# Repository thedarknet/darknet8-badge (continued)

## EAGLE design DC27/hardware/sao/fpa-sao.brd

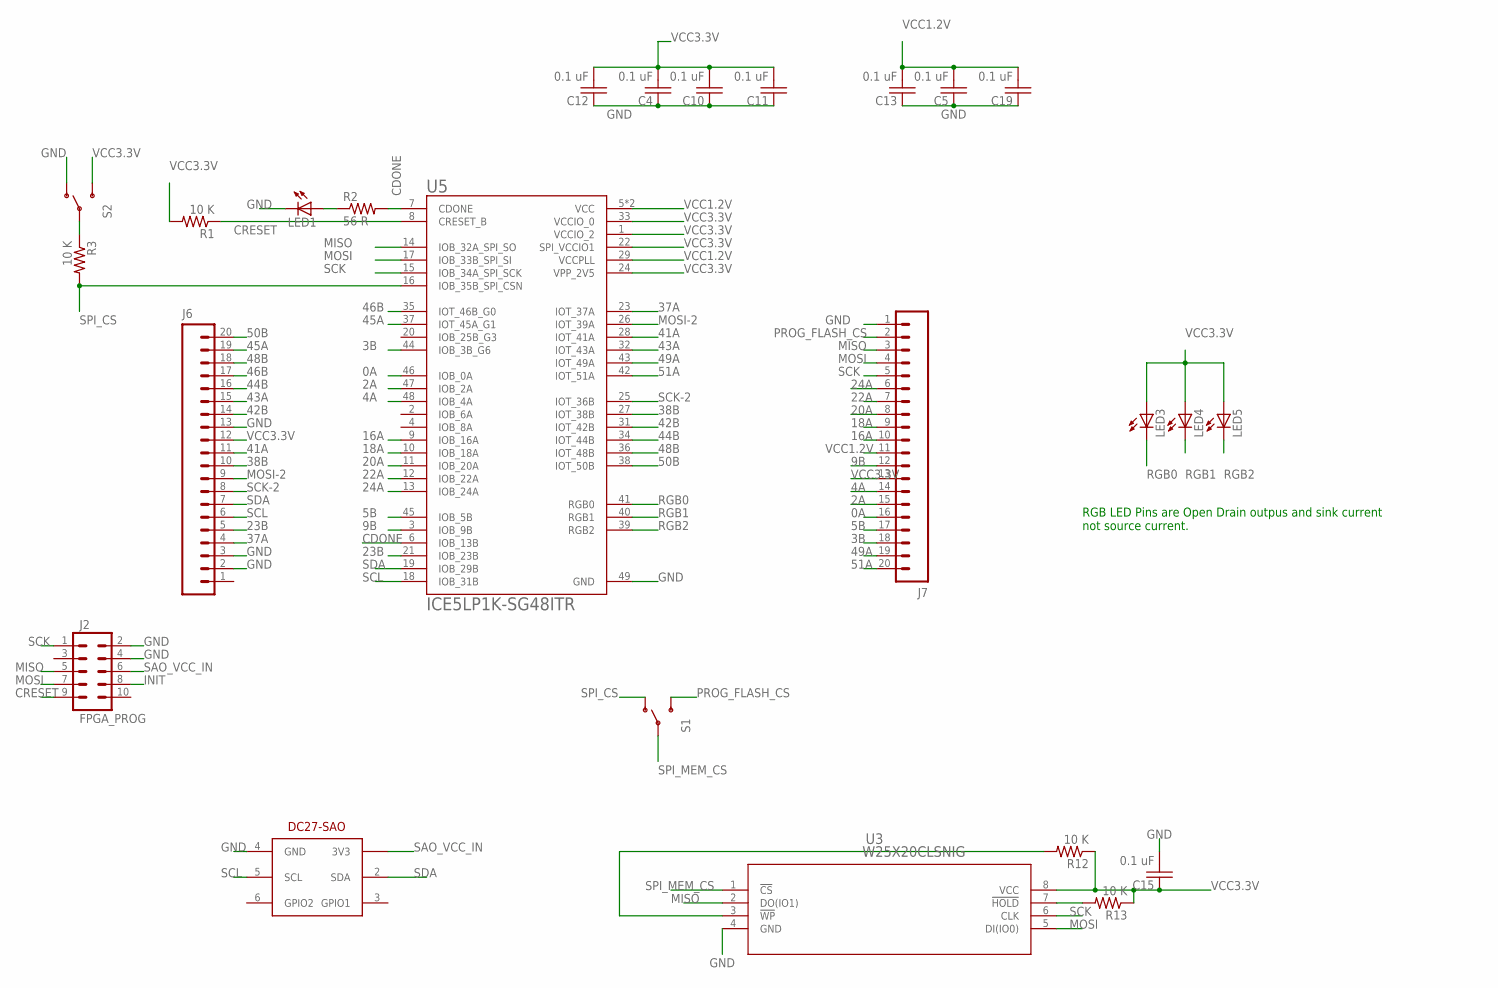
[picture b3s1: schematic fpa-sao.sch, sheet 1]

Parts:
C4, C5, C10, C11, C12, C13, C15, C19: 0.1 uF; C0603
J2: FPGA_PROG; 2X5_NOSILK
J6, J7: M20NO_SILK_KIT; 1X20_NO_SILK_KIT
LED1: LED1206; LED-1206
LED3, LED4, LED5: LED3MM
R1, R3, R12, R13: 10 K; 0805
R2: 56 R; 1206
S1, S2: SWITCH-SPSTKIT; SWITCH-SPDT_KIT
U3: W25X20CLSNIG; WIN_SN-8
U5: ICE5LP1K-SG48ITR; QFN50P700X700X100-49N
U$1: DC-27-SAO; 3X2

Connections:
0A: J7.16, U5.46 (IOB_0A)
2A: J7.15, U5.47 (IOB_2A)
3B: J7.18, U5.44 (IOB_3B_G6)
4A: J7.14, U5.48 (IOB_4A)
5B: J7.17, U5.45 (IOB_5B)
9B: J7.12, U5.3 (IOB_9B)
16A: J7.10, U5.9 (IOB_16A)
18A: J7.9, U5.10 (IOB_18A)
20A: J7.8, U5.11 (IOB_20A)
22A: J7.7, U5.12 (IOB_22A)
23B: J6.5, U5.21 (IOB_23B)
24A: J7.6, U5.13 (IOB_24A)
37A: J6.4, U5.23 (IOT_37A)
38B: J6.10, U5.27 (IOT_38B)
41A: J6.11, U5.28 (IOT_41A)
42B: J6.14, U5.31 (IOT_42B)
43A: J6.15, U5.32 (IOT_43A)
44B: J6.16, U5.34 (IOT_44B)
45A: J6.19, U5.37 (IOT_45A_G1)
46B: J6.17, U5.35 (IOT_46B_G0)
48B: J6.18, U5.36 (IOT_48B)
49A: J7.19, U5.43 (IOT_49A)
50B: J6.20, U5.38 (IOT_50B)
51A: J7.20, U5.42 (IOT_51A)
CDONE: R2.2, U5.6 (IOB_13B), U5.7 (CDONE)
CRESET: J2.9, R1.1, U5.8 (CRESET_B)
GND: C4.1, C5.1, C10.1, C11.1, C12.1, C13.1, C15.2, C19.1, J2.2, J2.4, J6.2, J6.3, J6.13, J7.1, LED1.C, S2.1 (O), U3.4 (GND), U5.49 (GND), U$1.4 (GND); also elsewhere on the board
INIT: J2.8
MISO: J2.5, J7.3, U3.2 (DO(IO1)), U5.14 (IOB_32A_SPI_SO)
MOSI: J2.7, J7.4, U3.5 (DI(IO0)), U5.17 (IOB_33B_SPI_SI); also elsewhere on the board
MOSI-2: J6.9, U5.26 (IOT_39A); also elsewhere on the board
unnamed: LED1.A, R2.1
unnamed: R3.1, S2.2
unnamed: R12.2, U3.3 (!WP)
unnamed: R13.2, U3.7 (!HOLD)
PROG_FLASH_CS: J7.2, S1.3 (S)
RGB0: LED3.K (C), U5.41 (RGB0)
RGB1: LED4.K (C), U5.40 (RGB1)
RGB2: LED5.K (C), U5.39 (RGB2)
SAO_VCC_IN: J2.6, U$1.1 (3V3); also elsewhere on the board
SCK: J2.1, J7.5, U3.6 (CLK), U5.15 (IOB_34A_SPI_SCK); also elsewhere on the board
SCK-2: J6.8, U5.25 (IOT_36B); also elsewhere on the board
SCL: J6.6, U5.18 (IOB_31B), U$1.5 (SCL)
SDA: J6.7, U5.19 (IOB_29B), U$1.2 (SDA)
SPI_CS: R3.2, S1.1 (O), U5.16 (IOB_35B_SPI_CSN)
SPI_MEM_CS: S1.2, U3.1 (!CS)
VCC1.2V: C5.2, C13.2, C19.2, J7.11, U5.5 (VCC), U5.29 (VCCPLL), U5.30 (VCC); also elsewhere on the board
VCC3.3V: C4.2, C10.2, C11.2, C12.2, C15.1, J6.12, J7.13, LED3.A, LED4.A, LED5.A, R1.2, R12.1, R13.1, S2.3 (S), U3.8 (VCC), U5.1 (VCCIO_2), U5.22 (SPI_VCCIO1), U5.24 (VPP_2V5), U5.33 (VCCIO_0); also elsewhere on the board

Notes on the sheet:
RGB LED Pins are Open Drain outpus and sink current not source current.

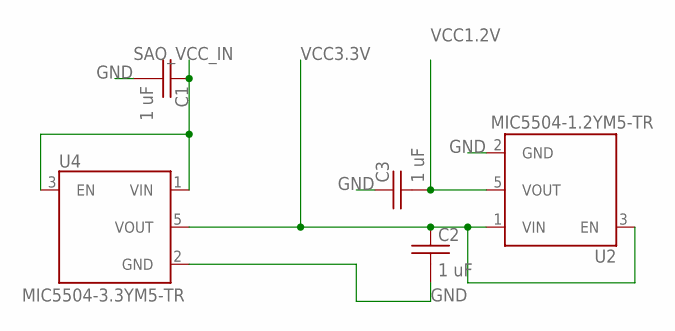
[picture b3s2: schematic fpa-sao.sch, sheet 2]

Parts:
C1, C2, C3: 1 uF; C0603
U2: MIC5504-1.2YM5-TR; SOT23-5P95_280X145XL45X37N
U4: MIC5504-3.3YM5-TR; SOT23-5P95_280X145XL45X37N

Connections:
GND: C1.2, C2.2, C3.1, U2.2 (GND), U4.2 (GND); also elsewhere on the board
SAO_VCC_IN: C1.1, U4.1 (VIN), U4.3 (EN); also elsewhere on the board
VCC1.2V: C3.2, U2.5 (VOUT); also elsewhere on the board
VCC3.3V: C2.1, U2.1 (VIN), U2.3 (EN), U4.5 (VOUT); also elsewhere on the board

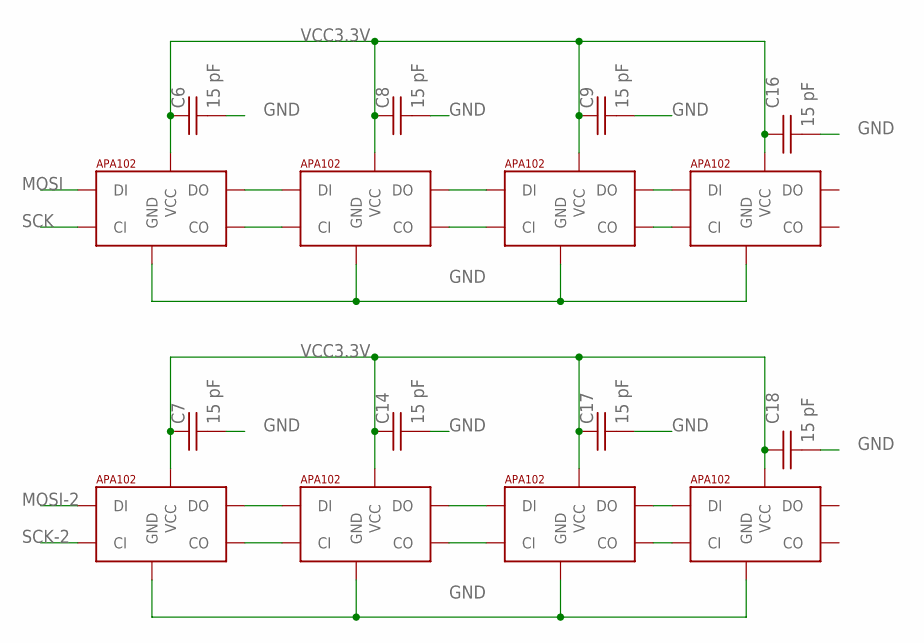
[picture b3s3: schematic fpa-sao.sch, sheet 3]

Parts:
C6, C7, C8, C9, C14, C16, C17, C18: 15 pF; C1206
U$2, U$3, U$4, U$5, U$6, U$7, U$8, U$10: APA1025050; APA102_5050

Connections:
GND: C6.2, C7.2, C8.2, C9.2, C14.2, C16.2, C17.2, C18.2, U$2.6 (GND), U$3.6 (GND), U$4.6 (GND), U$5.6 (GND), U$6.6 (GND), U$7.6 (GND), U$8.6 (GND), U$10.6 (GND); also elsewhere on the board
MOSI: U$6.4 (DI); also elsewhere on the board
MOSI-2: U$2.4 (DI); also elsewhere on the board
unnamed: U$6.2 (CO), U$7.5 (CI)
unnamed: U$6.3 (DO), U$7.4 (DI)
unnamed: U$7.3 (DO), U$8.4 (DI)
unnamed: U$7.2 (CO), U$8.5 (CI)
unnamed: U$2.2 (CO), U$3.5 (CI)
unnamed: U$8.3 (DO), U$10.4 (DI)
unnamed: U$8.2 (CO), U$10.5 (CI)
unnamed: U$2.3 (DO), U$3.4 (DI)
unnamed: U$3.3 (DO), U$4.4 (DI)
unnamed: U$3.2 (CO), U$4.5 (CI)
unnamed: U$4.3 (DO), U$5.4 (DI)
unnamed: U$4.2 (CO), U$5.5 (CI)
SCK: U$6.5 (CI); also elsewhere on the board
SCK-2: U$2.5 (CI); also elsewhere on the board
VCC3.3V: C6.1, C7.1, C8.1, C9.1, C14.1, C16.1, C17.1, C18.1, U$2.1 (VCC), U$3.1 (VCC), U$4.1 (VCC), U$5.1 (VCC), U$6.1 (VCC), U$7.1 (VCC), U$8.1 (VCC), U$10.1 (VCC); also elsewhere on the board

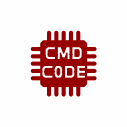
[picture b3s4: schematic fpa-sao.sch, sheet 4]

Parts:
U$9: CMD_C0DE_LOGOCMD_CODE_LOGO_SILK; CMD_C0DE_LOGO_SILK

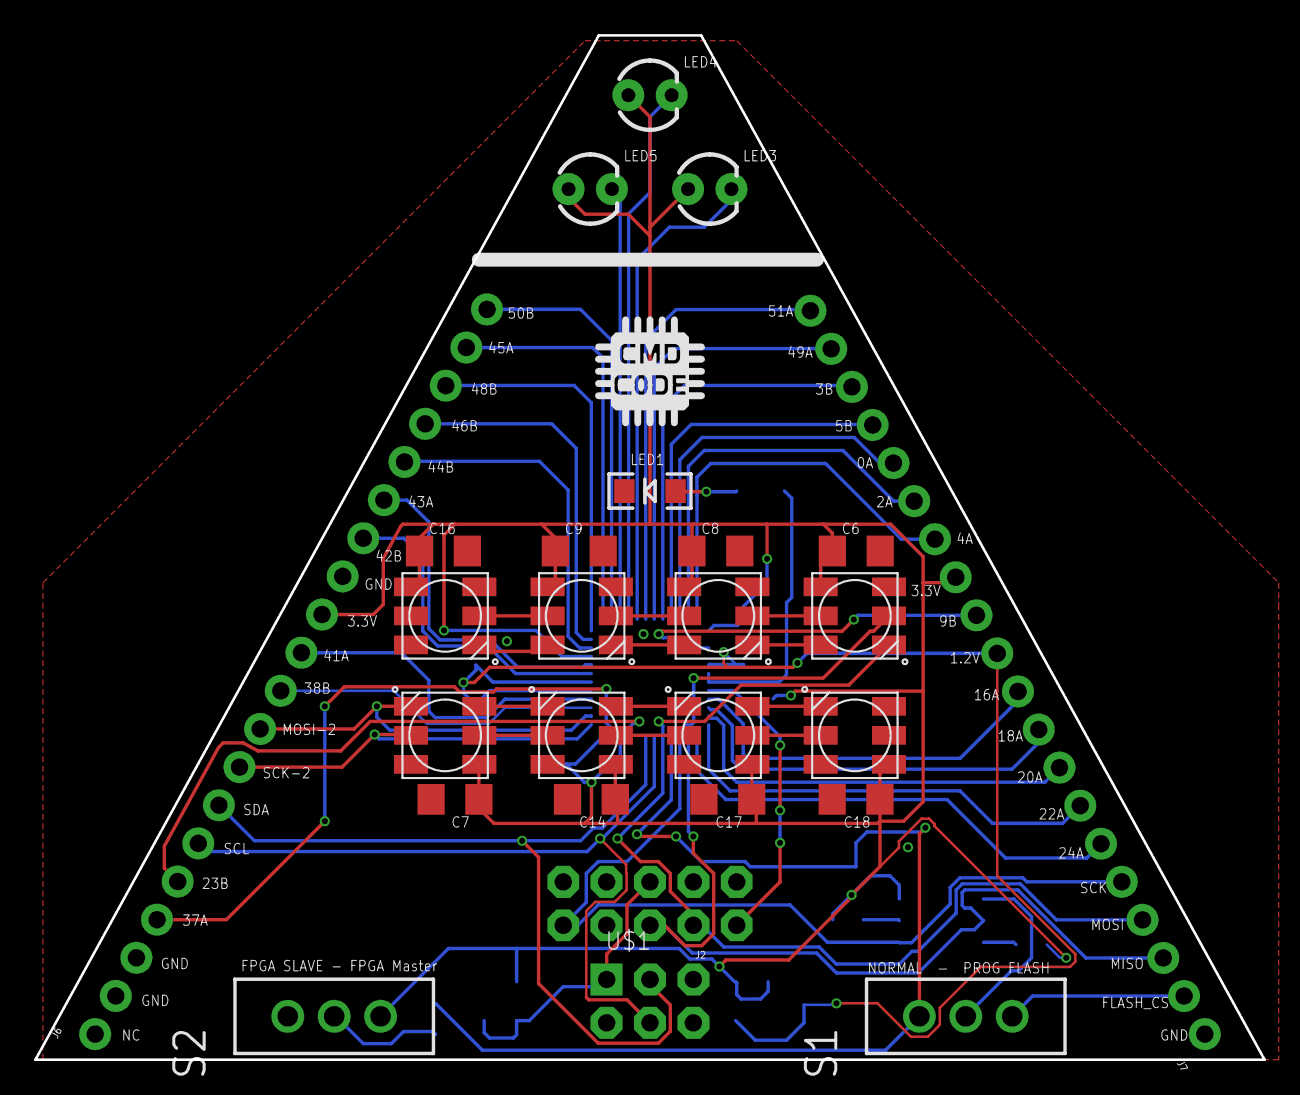
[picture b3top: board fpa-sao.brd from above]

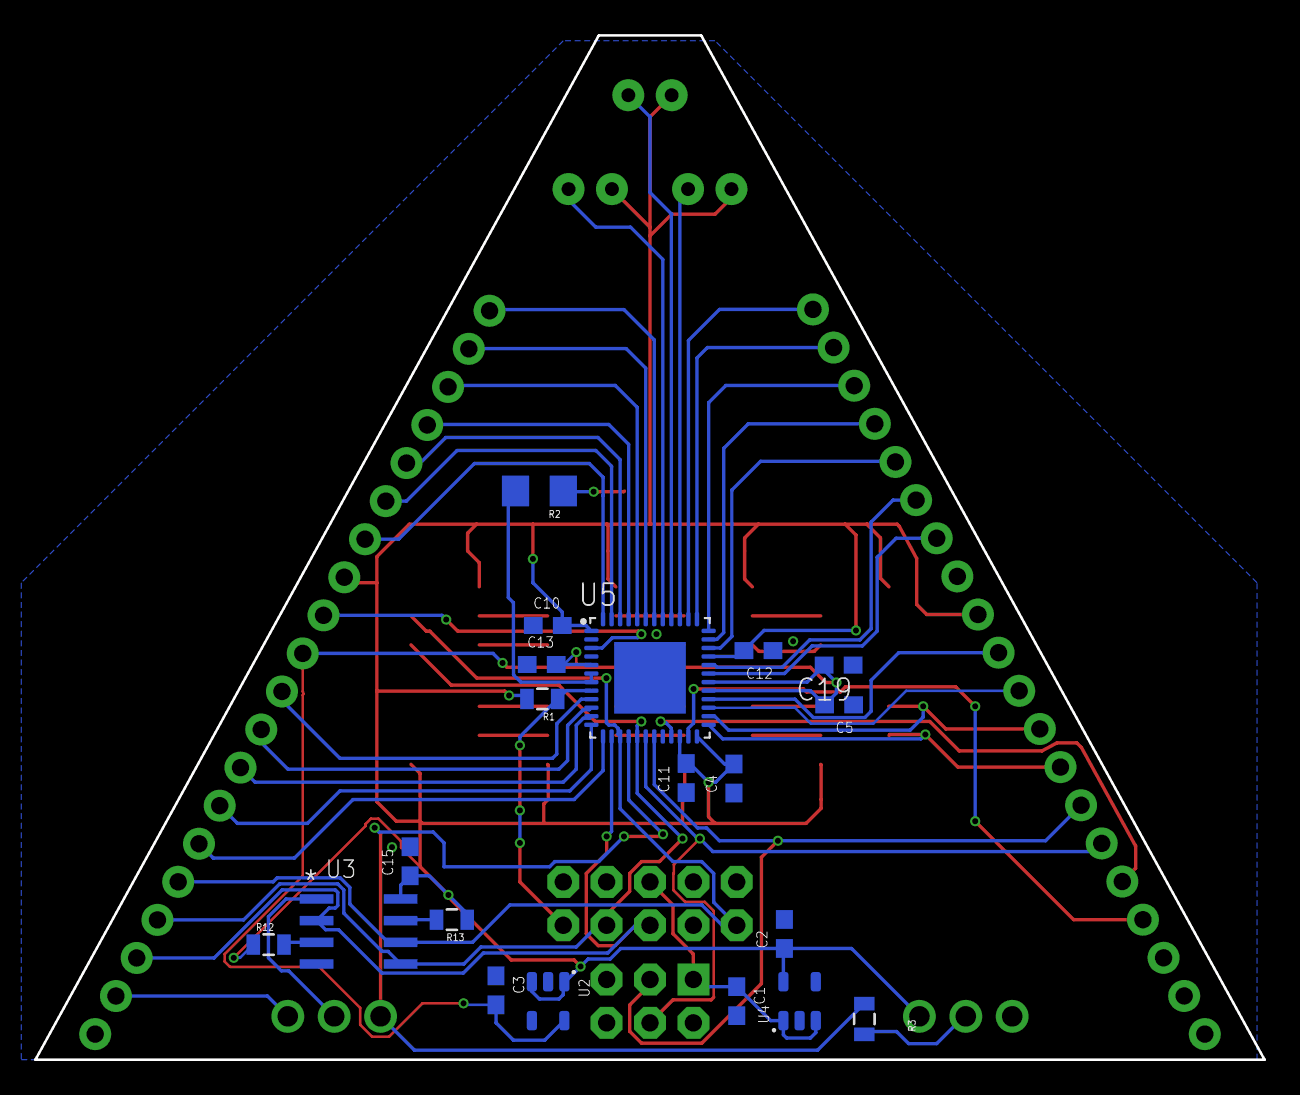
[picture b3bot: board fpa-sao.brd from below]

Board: 2 copper layers, 72.0 x 60.0 mm, 47 parts (20 on the bottom side), 59 nets.

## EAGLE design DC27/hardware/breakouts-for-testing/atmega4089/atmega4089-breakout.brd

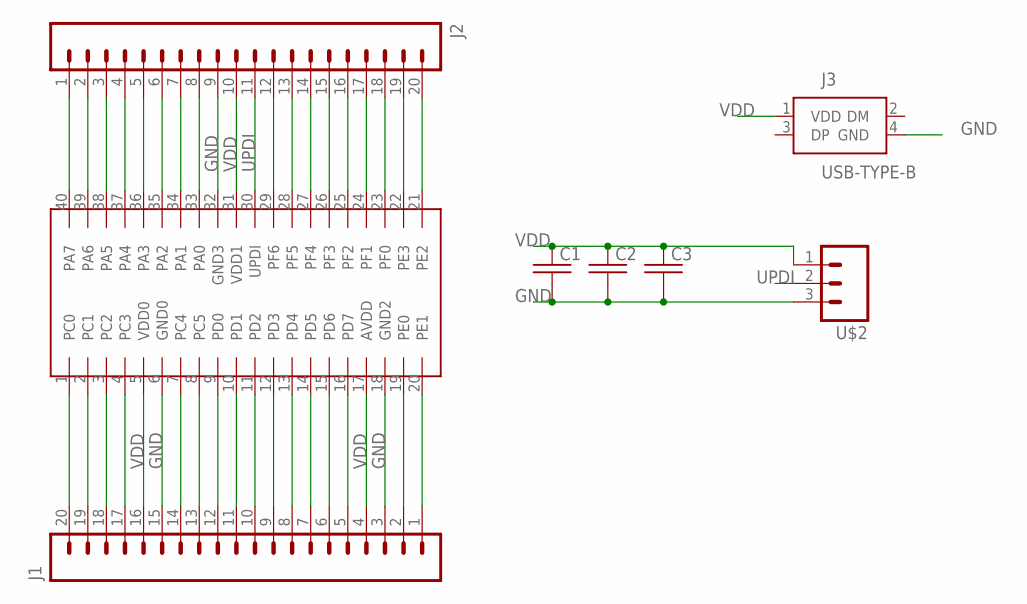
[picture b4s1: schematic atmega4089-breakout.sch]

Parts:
C1, C2, C3: C-USC0805; C0805
J1, J2: M20; 1X20
J3: USB-TYPE-B; 61400413321
U$1: ATMEGA4809-PFATMEL4809-PF; DIP1587W58P254L5175H635Q40B
U$2: M03; 1X03_UDPI

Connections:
GND: C1.2, C2.2, C3.2, J1.3, J1.15, J2.9, J3.4 (GND), U$1.6 (GND0), U$1.18 (GND2), U$1.32 (GND3), U$2.3
unnamed: J2.1, U$1.40 (PA7)
unnamed: J2.2, U$1.39 (PA6)
unnamed: J2.3, U$1.38 (PA5)
unnamed: J2.4, U$1.37 (PA4)
unnamed: J2.5, U$1.36 (PA3)
unnamed: J2.6, U$1.35 (PA2)
unnamed: J2.7, U$1.34 (PA1)
unnamed: J2.8, U$1.33 (PA0)
unnamed: J2.12, U$1.29 (PF6)
unnamed: J2.13, U$1.28 (PF5)
unnamed: J2.14, U$1.27 (PF4)
unnamed: J2.15, U$1.26 (PF3)
unnamed: J2.16, U$1.25 (PF2)
unnamed: J2.17, U$1.24 (PF1)
unnamed: J2.18, U$1.23 (PF0)
unnamed: J2.19, U$1.22 (PE3)
unnamed: J2.20, U$1.21 (PE2)
unnamed: J1.1, U$1.20 (PE1)
unnamed: J1.2, U$1.19 (PE0)
unnamed: J1.5, U$1.16 (PD7)
unnamed: J1.6, U$1.15 (PD6)
unnamed: J1.7, U$1.14 (PD5)
unnamed: J1.8, U$1.13 (PD4)
unnamed: J1.9, U$1.12 (PD3)
unnamed: J1.10, U$1.11 (PD2)
unnamed: J1.11, U$1.10 (PD1)
unnamed: J1.12, U$1.9 (PD0)
unnamed: J1.13, U$1.8 (PC5)
unnamed: J1.14, U$1.7 (PC4)
unnamed: J1.17, U$1.4 (PC3)
unnamed: J1.18, U$1.3 (PC2)
unnamed: J1.19, U$1.2 (PC1)
unnamed: J1.20, U$1.1 (PC0)
UPDI: J2.11, U$1.30 (UPDI), U$2.2
VDD: C1.1, C2.1, C3.1, J1.4, J1.16, J2.10, J3.1 (VDD), U$1.5 (VDD0), U$1.17 (AVDD), U$1.31 (VDD1), U$2.1

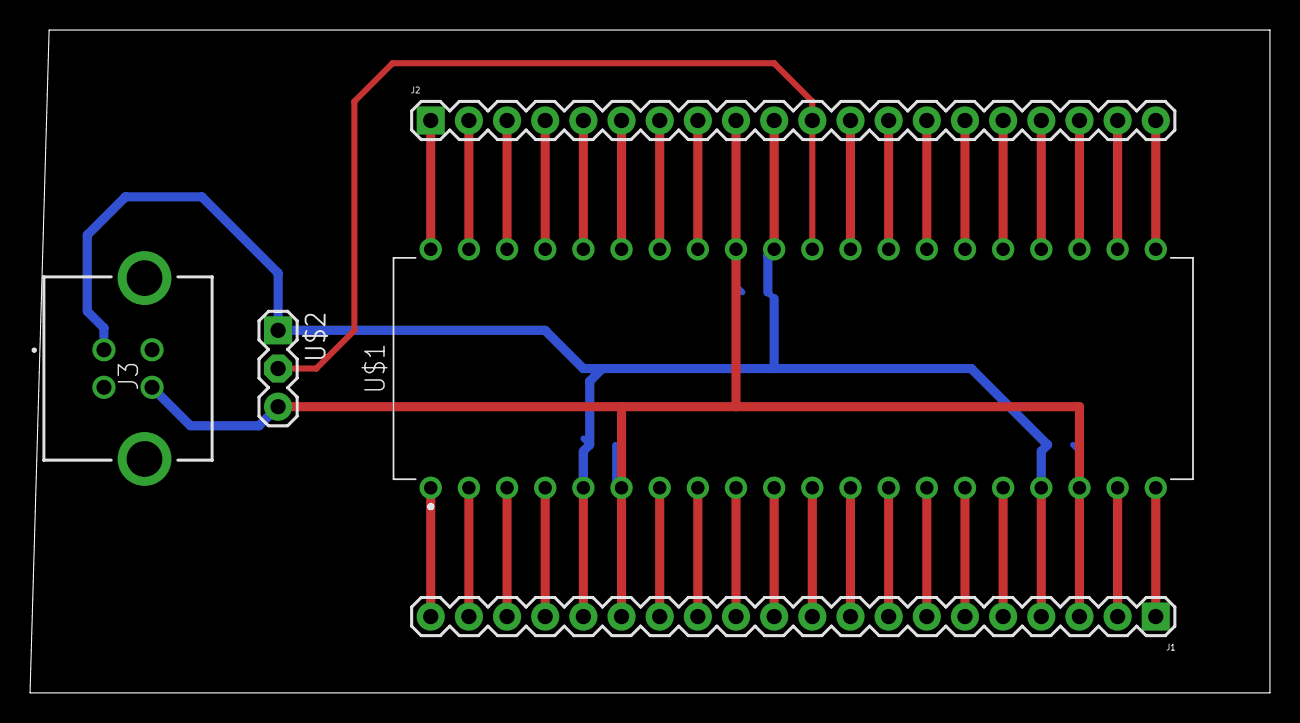
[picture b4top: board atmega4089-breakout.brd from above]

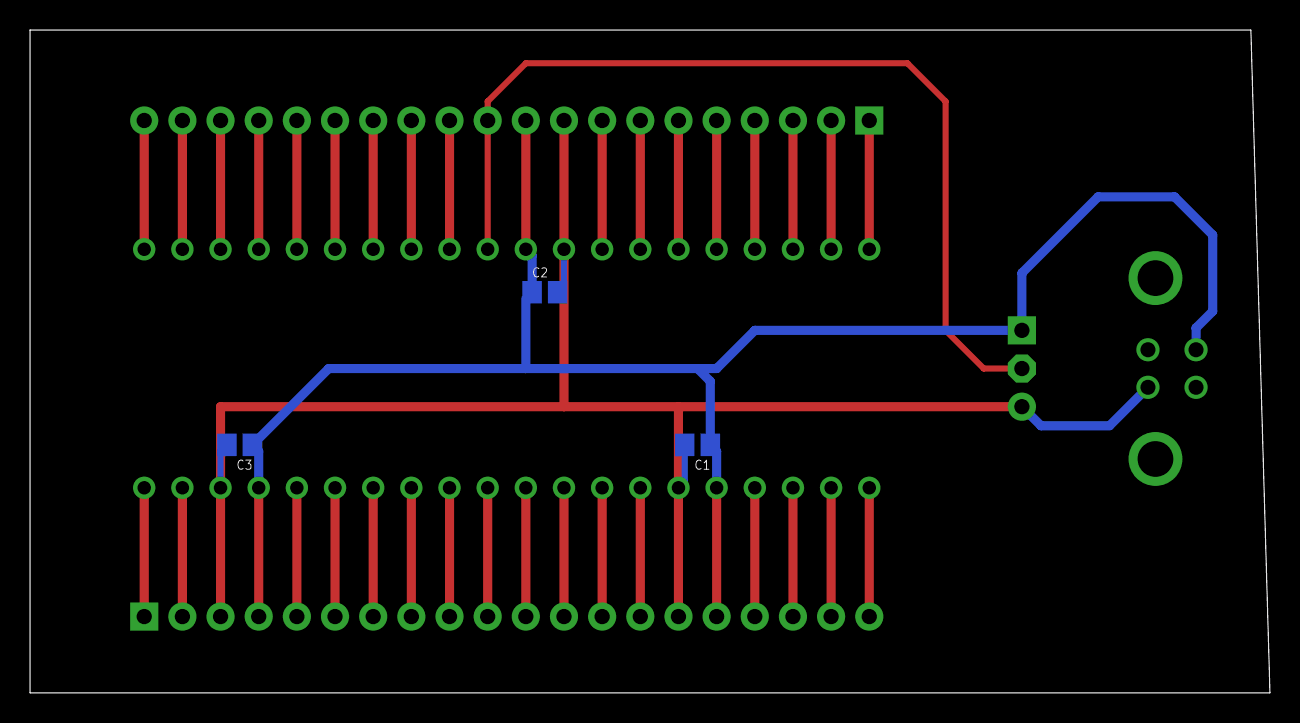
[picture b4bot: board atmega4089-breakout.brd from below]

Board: 2 copper layers, 82.5 x 44.1 mm, 8 parts (3 on the bottom side), 36 nets.

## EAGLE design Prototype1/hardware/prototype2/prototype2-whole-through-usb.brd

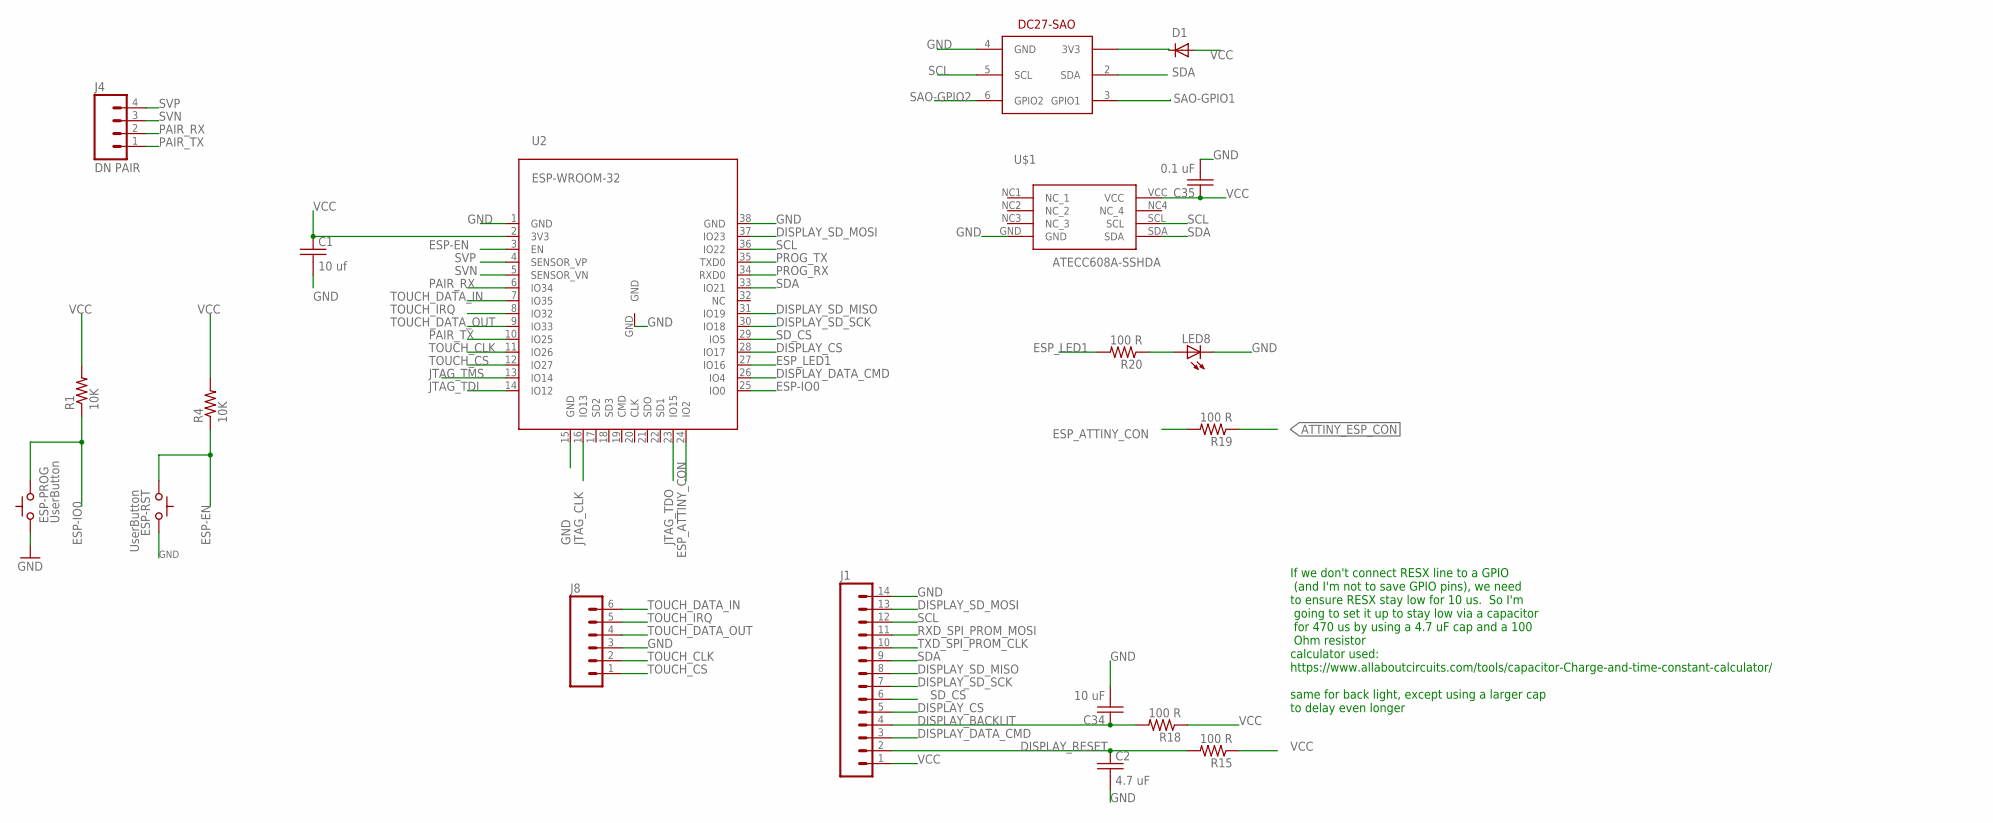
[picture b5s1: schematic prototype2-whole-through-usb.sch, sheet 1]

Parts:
C1: 10 uf; C0805
C2: 4.7 uF; C0805
C34: 10 uF; C0805
C35: 0.1 uF; C0805
D1: DIODESMA; SMA-DIODE
ESP-PROG: UserButton; TACTILE-2PIN-NARROW
ESP-RST: UserButton; TACTILE-2PIN-NARROW
J1: M14; 1X14
J4: DN PAIR; 1X04
J8: M06NO_SILK_YES_STOP; 1X06_NO_SILK_YES_STOP
LED8: LED3MM
R1, R4: 10K; 0805
R15, R18, R19, R20: 100 R; 0805
U2: ESP-WROOM-32
U$1: ATECC608A-SSHDA; 8-SOIC
U$4: DC-27-SAO; 3X2

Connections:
ATTINY_ESP_CON: R19.1; also elsewhere on the board
DISPLAY_BACKLIT: C34.1, J1.4, R18.2
DISPLAY_CS: J1.5, U2.28 (IO17)
DISPLAY_DATA_CMD: J1.3, U2.26 (IO4)
DISPLAY_RESET: C2.1, J1.2, R15.2
DISPLAY_SD_MISO: J1.8, U2.31 (IO19)
DISPLAY_SD_MOSI: J1.13, U2.37 (IO23)
DISPLAY_SD_SCK: J1.7, U2.30 (IO18)
ESP-EN: ESP-RST.P$2 (C), R4.1, U2.3 (EN)
ESP-IO0: ESP-PROG.P$1 (A), R1.1, U2.25 (IO0)
ESP_ATTINY_CON: R19.2, U2.24 (IO2)
ESP_LED1: R20.2, U2.27 (IO16)
GND: C1.2, C2.2, C34.2, C35.2, ESP-PROG.P$2 (C), ESP-RST.P$1 (A), J1.14, J8.3, LED8.K (C), U2.1 (GND), U2.15 (GND), U2.38 (GND), U2.GND, U$1.GND, U$4.4 (GND); also elsewhere on the board
JTAG_CLK: U2.16 (IO13); also elsewhere on the board
JTAG_TDI: U2.14 (IO12); also elsewhere on the board
JTAG_TDO: U2.23 (IO15); also elsewhere on the board
JTAG_TMS: U2.13 (IO14); also elsewhere on the board
unnamed: D1.C, U$4.1 (3V3)
unnamed: LED8.A, R20.1
PAIR_RX: J4.2, U2.6 (IO34)
PAIR_TX: J4.1, U2.10 (IO25)
PROG_RX: U2.34 (RXD0); also elsewhere on the board
PROG_TX: U2.35 (TXD0); also elsewhere on the board
RXD_SPI_PROM_MOSI: J1.11; also elsewhere on the board
SAO-GPIO1: U$4.3 (GPIO1)
SAO-GPIO2: U$4.6 (GPIO2)
SCL: J1.12, U2.36 (IO22), U$1.SCL, U$4.5 (SCL)
SDA: J1.9, U2.33 (IO21), U$1.SDA, U$4.2 (SDA)
SD_CS: J1.6, U2.29 (IO5)
SVN: J4.3, U2.5 (SENSOR_VN)
SVP: J4.4, U2.4 (SENSOR_VP)
TOUCH_CLK: J8.2, U2.11 (IO26)
TOUCH_CS: J8.1, U2.12 (IO27)
TOUCH_DATA_IN: J8.6, U2.7 (IO35)
TOUCH_DATA_OUT: J8.4, U2.9 (IO33)
TOUCH_IRQ: J8.5, U2.8 (IO32)
TXD_SPI_PROM_CLK: J1.10; also elsewhere on the board
VCC: C1.1, C35.1, D1.A, J1.1, R1.2, R4.2, R15.1, R18.1, U2.2 (3V3), U$1.VCC; also elsewhere on the board

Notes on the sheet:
If we don't connect RESX line to a GPIO (and I'm not to save GPIO pins), we need to ensure RESX stay low for 10 us. So I'm going to set it up to stay low via a capacitor for 470 us by using a 4.7 uF cap and a 100 Ohm resistor calculator used: https://www.allaboutcircuits.com/tools/capacitor-Charge-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

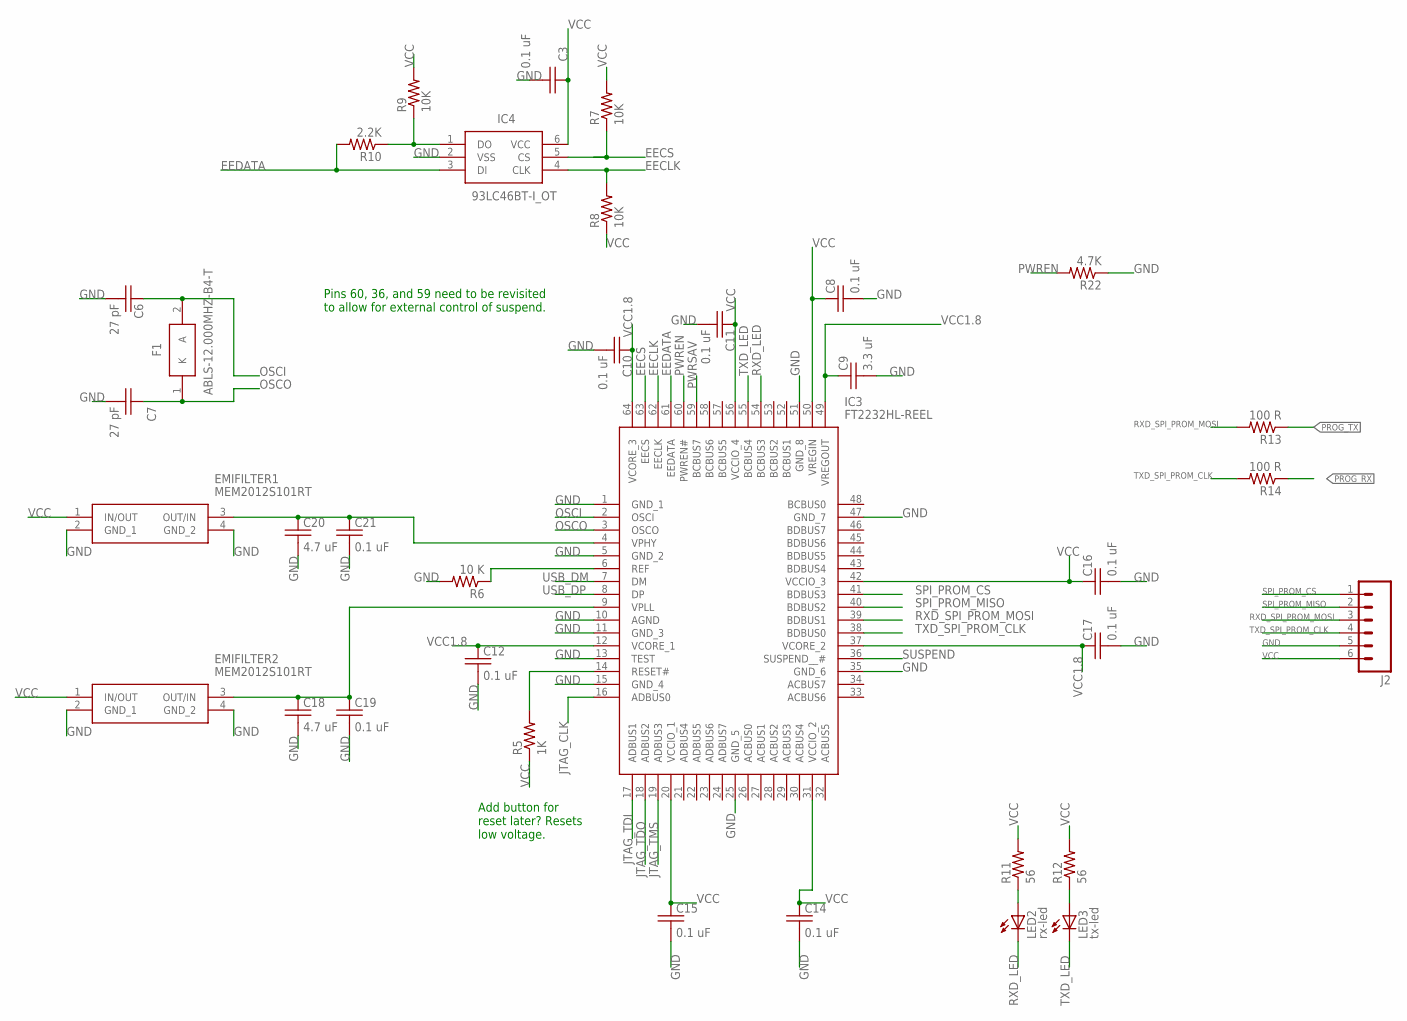
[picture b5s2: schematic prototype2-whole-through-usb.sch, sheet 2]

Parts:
C3, C8, C10, C11, C12, C14, C15, C16, C17, C19, C21: 0.1 uF; C0805
C6, C7: 27 pF; C0805
C9: 3.3 uF; C0805
C18, C20: 4.7 uF; C0805
EMIFILTER1, EMIFILTER2: MEM2012S101RT
F1: ABLS-12.000MHZ-B4-T; HC/49US-(AT49)_1
IC3: FT2232HL-REEL; QFP50P1200X1200X160-64N
IC4: 93LC46BT-I_OT; SOT95P270X145-6N
J2: M06SILK_FEMALE_PTH; 1X06
LED2: rx-led; LED3MM
LED3: tx-led; LED3MM
R5: 1K; 0805
R6: 10 K; 0805
R7, R8, R9: 10K; 0805
R10: 2.2K; 0805
R11, R12: 56; 0805
R13, R14: 100 R; 0805
R22: 4.7K; 0805

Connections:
EECLK: IC3.62 (EECLK), IC4.4 (CLK), R8.2
EECS: IC3.63 (EECS), IC4.5 (CS), R7.1
EEDATA: IC3.61 (EEDATA), IC4.3 (DI), R10.2
GND: C3.2, C6.2, C7.2, C8.2, C9.2, C10.2, C11.2, C12.2, C14.2, C15.2, C16.2, C17.2, C18.2, C19.2, C20.2, C21.2, EMIFILTER1.2 (GND_1), EMIFILTER1.4 (GND_2), EMIFILTER2.2 (GND_1), EMIFILTER2.4 (GND_2), IC3.1 (GND_1), IC3.5 (GND_2), IC3.10 (AGND), IC3.11 (GND_3), IC3.13 (TEST), IC3.15 (GND_4), IC3.25 (GND_5), IC3.35 (GND_6), IC3.47 (GND_7), IC3.51 (GND_8), IC4.2 (VSS), J2.5, R6.2, R22.1; also elsewhere on the board
JTAG_CLK: IC3.16 (ADBUS0); also elsewhere on the board
JTAG_TDI: IC3.17 (ADBUS1); also elsewhere on the board
JTAG_TDO: IC3.18 (ADBUS2); also elsewhere on the board
JTAG_TMS: IC3.19 (ADBUS3); also elsewhere on the board
unnamed: IC3.14 (RESET#), R5.2
unnamed: IC3.6 (REF), R6.1
unnamed: IC4.1 (DO), R9.1, R10.1
unnamed: LED2.A, R11.1
unnamed: LED3.A, R12.1
unnamed: C18.1, C19.1, EMIFILTER2.3 (OUT/IN), IC3.9 (VPLL)
unnamed: C20.1, C21.1, EMIFILTER1.3 (OUT/IN), IC3.4 (VPHY)
OSCI: C6.1, F1.2 (A), IC3.2 (OSCI)
OSCO: C7.1, F1.1 (K), IC3.3 (OSCO)
PROG_RX: R14.1; also elsewhere on the board
PROG_TX: R13.1; also elsewhere on the board
PWREN: IC3.60 (PWREN#), R22.2
PWRSAV: IC3.59 (BCBUS7)
RXD_LED: IC3.54 (BCBUS3), LED2.K (C)
RXD_SPI_PROM_MOSI: IC3.39 (BDBUS1), J2.3, R13.2; also elsewhere on the board
SPI_PROM_CS: IC3.41 (BDBUS3), J2.1
SPI_PROM_MISO: IC3.40 (BDBUS2), J2.2
SUSPEND: IC3.36 (SUSPEND__#)
TXD_LED: IC3.55 (BCBUS4), LED3.K (C)
TXD_SPI_PROM_CLK: IC3.38 (BDBUS0), J2.4, R14.2; also elsewhere on the board
USB_DM: IC3.7 (DM); also elsewhere on the board
USB_DP: IC3.8 (DP); also elsewhere on the board
VCC: C3.1, C8.1, C11.1, C14.1, C15.1, C16.1, EMIFILTER1.1 (IN/OUT), EMIFILTER2.1 (IN/OUT), IC3.20 (VCCIO_1), IC3.31 (VCCIO_2), IC3.42 (VCCIO_3), IC3.50 (VREGIN), IC3.56 (VCCIO_4), IC4.6 (VCC), J2.6, R5.1, R7.2, R8.1, R9.2, R11.2, R12.2; also elsewhere on the board
VCC1.8: C9.1, C10.1, C12.1, C17.1, IC3.12 (VCORE_1), IC3.37 (VCORE_2), IC3.49 (VREGOUT), IC3.64 (VCORE_3)

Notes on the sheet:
Add button for reset later? Resets low voltage.
Pins 60, 36, and 59 need to be revisited to allow for external control of suspend.

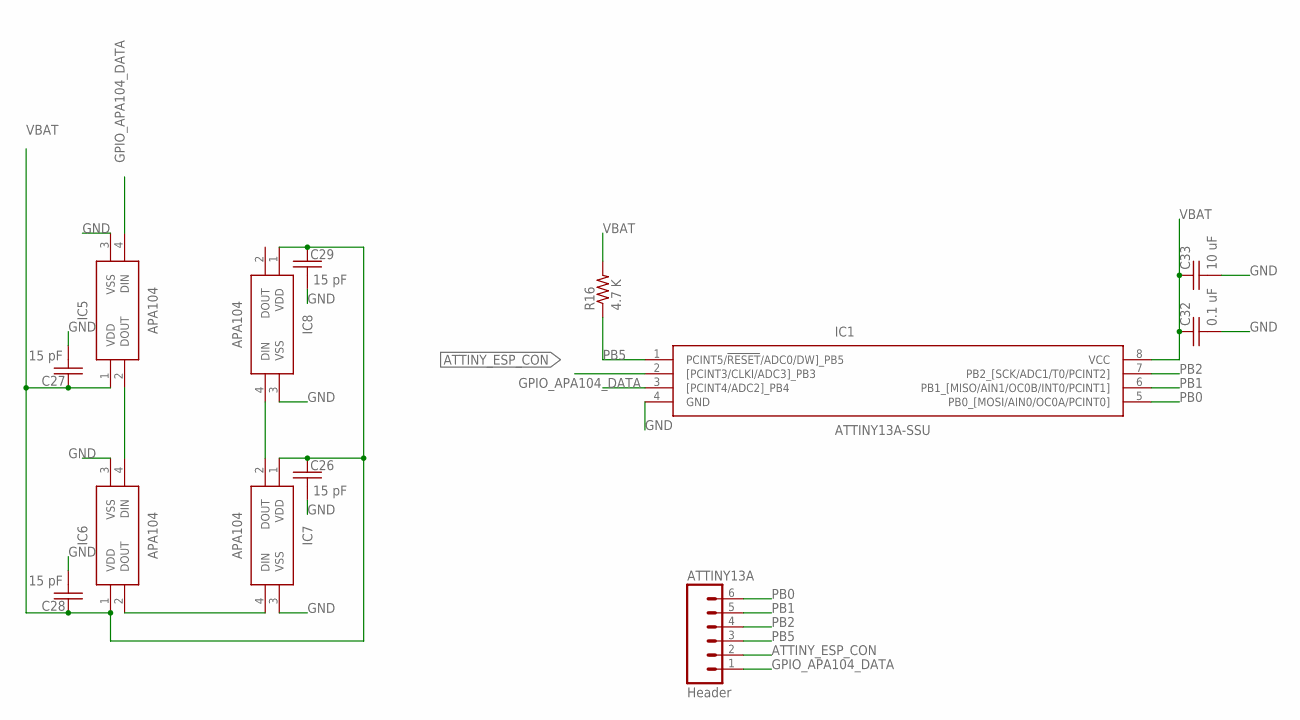
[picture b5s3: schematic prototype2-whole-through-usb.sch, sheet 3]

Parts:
ATTINY13A: Header; 1X06
C26, C27, C28, C29: 15 pF; C0805
C32: 0.1 uF; C0805
C33: 10 uF; C0805
IC1: ATTINY13A-SSU; SOIC127P600X175-8N
IC5, IC6, IC7, IC8: APA104
R16: 4.7 K; 0805

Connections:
ATTINY_ESP_CON: ATTINY13A.2, IC1.2 ([PCINT3/CLKI/ADC3]_PB3); also elsewhere on the board
GND: C26.2, C27.2, C28.2, C29.2, C32.2, C33.2, IC1.4 (GND), IC5.3 (VSS), IC6.3 (VSS), IC7.3 (VSS), IC8.3 (VSS); also elsewhere on the board
GPIO_APA104_DATA: ATTINY13A.1, IC1.3 ([PCINT4/ADC2]_PB4), IC5.4 (DIN)
unnamed: IC5.2 (DOUT), IC6.4 (DIN)
unnamed: IC6.2 (DOUT), IC7.4 (DIN)
unnamed: IC7.2 (DOUT), IC8.4 (DIN)
PB0: ATTINY13A.6, IC1.5 (PB0_[MOSI/AIN0/OC0A/PCINT0])
PB1: ATTINY13A.5, IC1.6 (PB1_[MISO/AIN1/OC0B/INT0/PCINT1])
PB2: ATTINY13A.4, IC1.7 (PB2_[SCK/ADC1/T0/PCINT2])
PB5: ATTINY13A.3, IC1.1 (PCINT5/!RESET!/ADC0/DW]_PB5), R16.1
VBAT: C26.1, C27.1, C28.1, C29.1, C32.1, C33.1, IC1.8 (VCC), IC5.1 (VDD), IC6.1 (VDD), IC7.1 (VDD), IC8.1 (VDD), R16.2; also elsewhere on the board

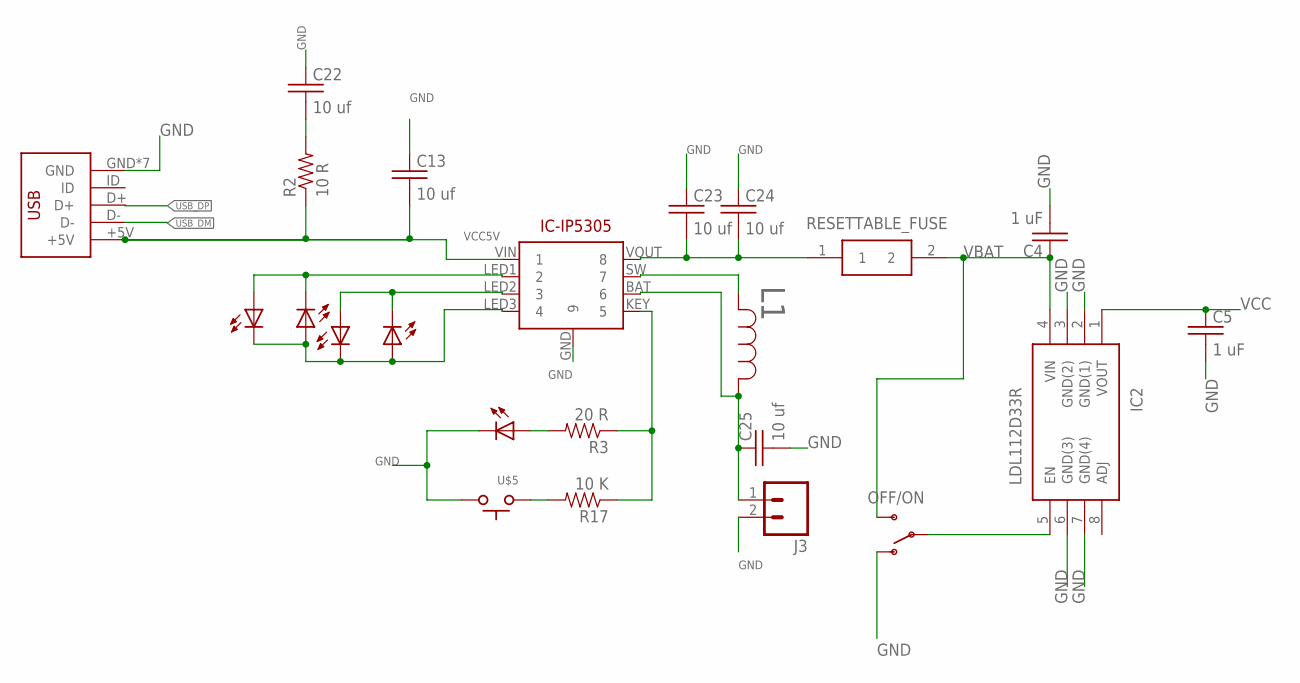
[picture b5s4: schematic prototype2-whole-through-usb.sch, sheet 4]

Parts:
C4, C5: 1 uF; C0805
C13, C22, C23, C24, C25: 10 uf; C0805
IC2: LDL112D33R; SOIC127P600X175-8N
IC-IP5305: IP5305ESOP8; SOIC127P600X165-8
J3: M02PTH; 1X02
L1: NRS4018T2R2MDGJ; IND_TAIYO_NRS4018
LED1, LED4, LED5, LED6, LED7: LED3MM
OFF/ON: SWITCH-SPSTKIT; SWITCH-SPDT_KIT
R2: 10 R; 0805
R3: 20 R; 0805
R17: 10 K; 0805
RESETTABLE_FUSE: 0ZCJ0050FF2G; FUSC3216X55N
U$2: DX4R005JJ2DX4R005JJ2; DX4R005JJ2
U$5: SWITCH_TACTILETACTILE-2PIN-NARROW; TACTILE-2PIN-NARROW

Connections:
GND: C4.2, C5.2, C13.1, C22.1, C23.1, C24.1, C25.2, IC2.2 (GND(1)), IC2.3 (GND(2)), IC2.6 (GND(3)), IC2.7 (GND(4)), IC-IP5305.GND (9), J3.2, LED7.K (C), OFF/ON.1 (O), U$2.GND, U$2.P$6 (GND), U$2.P$7 (GND), U$2.P$8 (GND), U$2.P$9 (GND), U$2.P$10 (GND), U$2.P$11 (GND), U$5.P$1 (A); also elsewhere on the board
unnamed: IC2.5 (EN), OFF/ON.2
unnamed: IC-IP5305.LED1 (2), LED1.A, LED4.K (C)
unnamed: C23.2, C24.2, IC-IP5305.VOUT (8), RESETTABLE_FUSE.1
unnamed: IC-IP5305.LED2 (3), LED5.A, LED6.K (C)
unnamed: IC-IP5305.LED3 (4), LED1.K (C), LED4.A, LED5.K (C), LED6.A
unnamed: C22.2, R2.2
unnamed: IC-IP5305.SW (7), L1.2
unnamed: C25.1, IC-IP5305.BAT (6), J3.1, L1.1
unnamed: IC-IP5305.KEY (5), R3.1, R17.1
unnamed: LED7.A, R3.2
unnamed: R17.2, U$5.P$2 (C)
USB_DM: U$2.D-; also elsewhere on the board
USB_DP: U$2.D+; also elsewhere on the board
VBAT: C4.1, IC2.4 (VIN), OFF/ON.3 (S), RESETTABLE_FUSE.2; also elsewhere on the board
VCC: C5.1, IC2.1 (VOUT); also elsewhere on the board
VCC5V: C13.2, IC-IP5305.VIN (1), R2.1, U$2.+5V

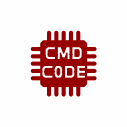
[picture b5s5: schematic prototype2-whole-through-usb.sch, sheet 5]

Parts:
U$3: CMD_C0DE_LOGOCMD_CODE_LOGO_TOP_COPPER; CMD_C0DE_LOGO_TOP_COPPER

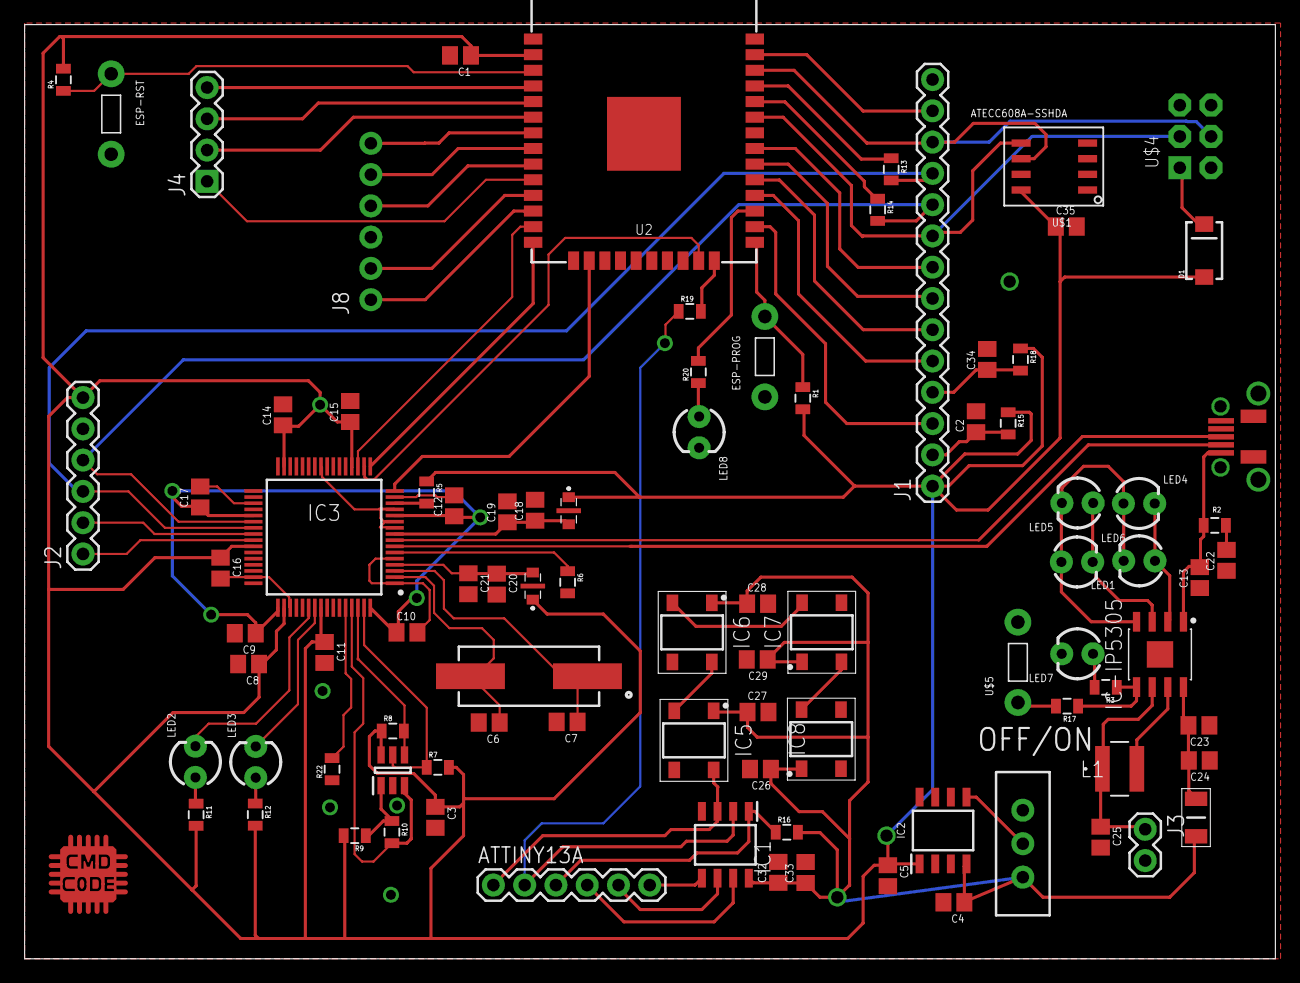
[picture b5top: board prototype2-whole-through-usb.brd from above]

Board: 2 copper layers, 101.6 x 75.9 mm, 92 parts (0 on the bottom side), 77 nets.
